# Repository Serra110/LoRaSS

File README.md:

**LoRaSS**

LoRaSS is a custom communication device built around LoRa technology, allowing two (or more) devices to exchange short messages over radio. It features five buttons: four for entering messages using a custom input system and one dedicated button to save or send the composed message, allowing an entire message to be transmitted in a single operation. The device also includes a display to preview outgoing messages and read received ones, as well as an LED and a buzzer to provide visual and audio feedback when messages are received (like a morse code machine).

**Features**

- **LoRa Communication:** Exchange messages wirelessly using LoRa radio technology.
- **Message Input:** Four buttons are used to enter the desired characters.
- **OLED Display:** Preview messages before sending and read incoming messages.
- **Misc:** An LED and a buzzer indicate when a message is received.

**Hardware Design**

The device is powered by a Raspberry Pi Pico (as mentioned in the other repos, it is my favorite board) and uses a LoRa radio module for wireless communication. The PCB integrates the display, buttons, buzzer, LED and antenna circuitry.

**3D Model**

A 3D representation of the project designed in KiCad.

**Schematic**

**Controls**

- **Buttons 1–4:** Enter characters to compose a message.
- **Button 5:** Send it to another device.

**Communication**

**Code**

The firmware runs on the Raspberry Pi Pico and handles message input.

**About the Project**

This project is my first time messing with antennas, and it is also my first experience working with SMD components and designing an antenna section as part of a PCB.

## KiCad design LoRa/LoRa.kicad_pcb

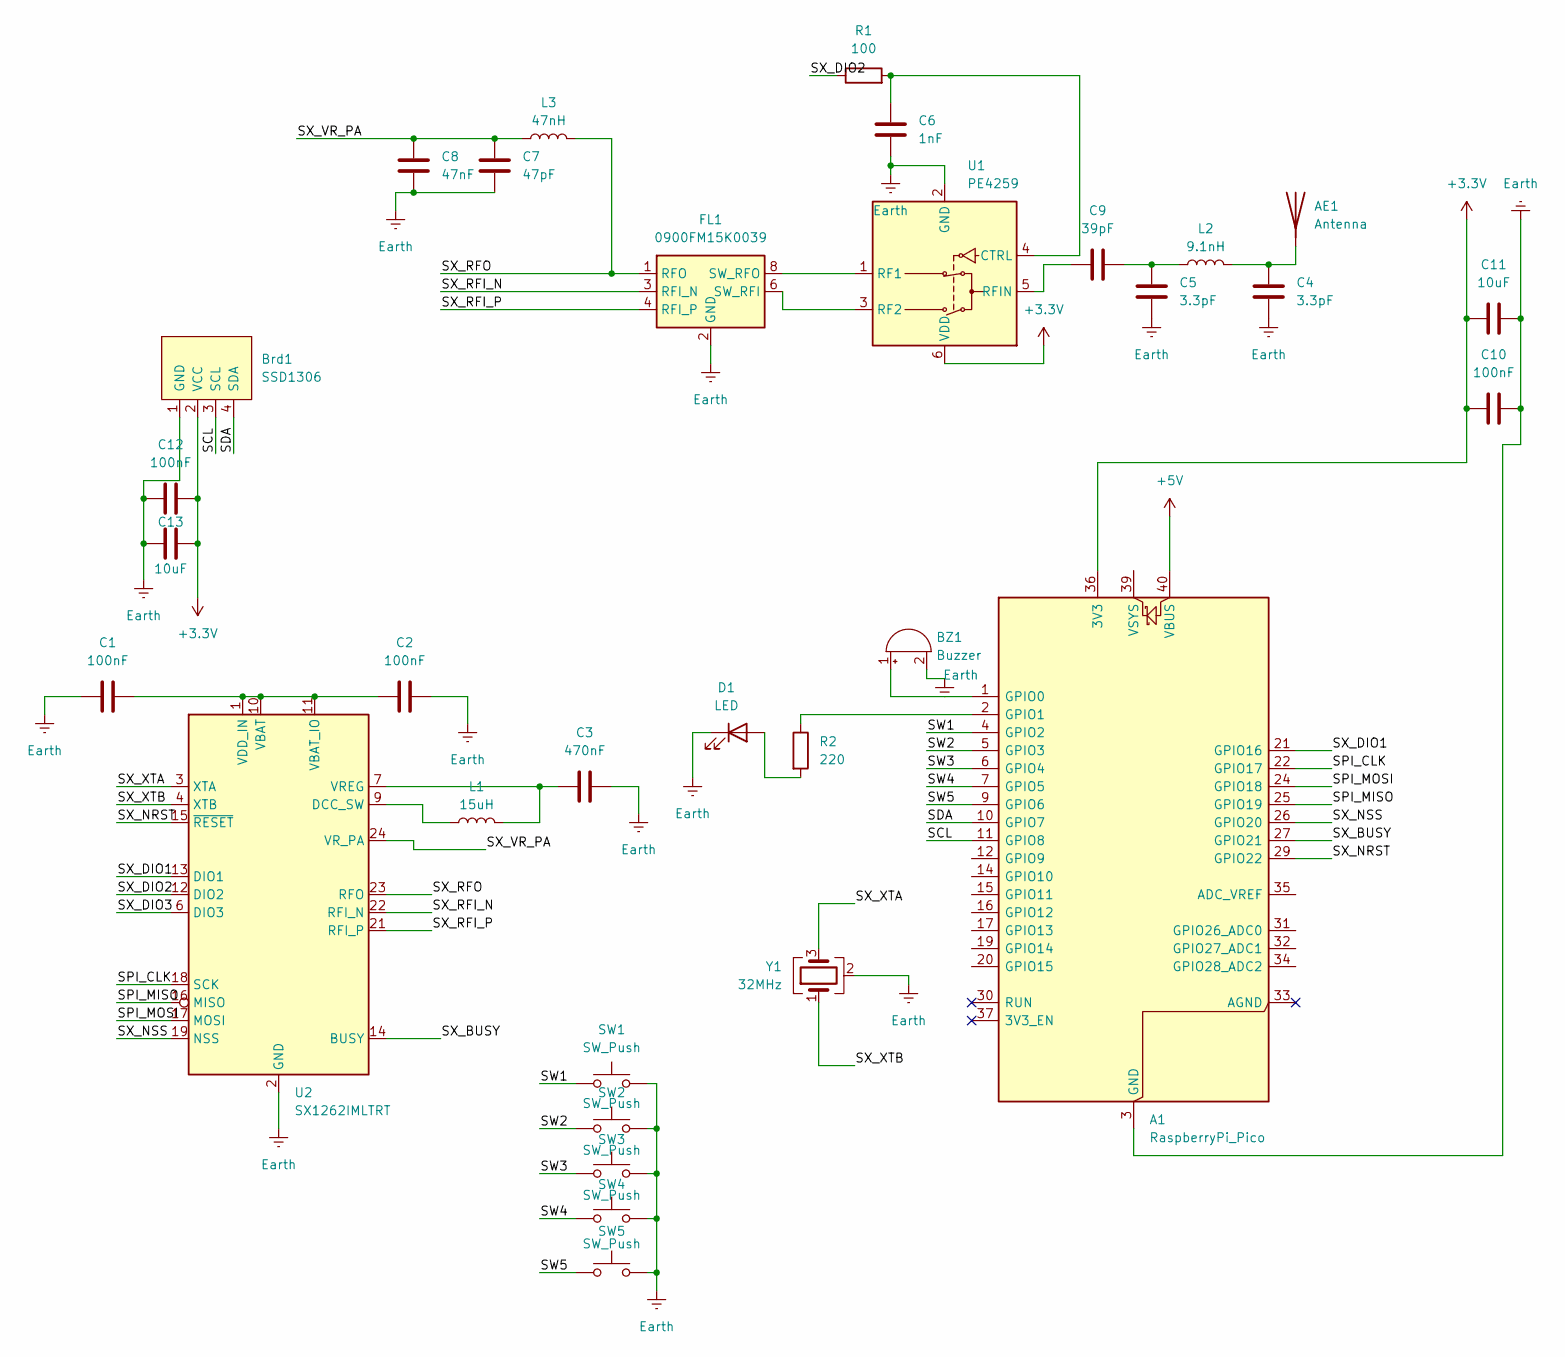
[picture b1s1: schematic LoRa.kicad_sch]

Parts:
A1: RaspberryPi_Pico; RaspberryPi_Pico_Common
AE1: Antenna; PinSocket_1x01_P2.54mm_Vertical
BZ1: Buzzer; Buzzer_12x9.5RM7.6
Brd1: SSD1306; 128x64OLED
C1, C2, C10, C12: 100nF; C_0402_1005Metric
C3: 470nF; C_0402_1005Metric
C4, C5: 3.3pF; C_0402_1005Metric
C6: 1nF; C_0402_1005Metric
C7: 47pF; C_0402_1005Metric
C8: 47nF; C_0402_1005Metric
C9: 39pF; C_0402_1005Metric
C11, C13: 10uF; C_0402_1005Metric
D1: LED; LED_D5.0mm
FL1: 0900FM15K0039; Balun_Johanson_0900FM15K0039
L1: 15uH; L_0402_1005Metric
L2: 9.1nH; L_0402_1005Metric
L3: 47nH; L_0402_1005Metric
R1: 100; R_0402_1005Metric
R2: 220; R_0402_1005Metric
SW1, SW2, SW3, SW4, SW5: SW_Push; SW_PUSH_6mm_H4.3mm
U1: PE4259; SOT-363_SC-70-6
U2: SX1262IMLTRT; QFN-24-1EP_4x4mm_P0.5mm_EP2.6x2.6mm
Y1: 32MHz; Crystal_SMD_3225-4Pin_3.2x2.5mm

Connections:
+3.3V: A1.36 (3V3), Brd1.2 (VCC), C10.1, C11.1, C12.2, C13.2, U1.6 (VDD)
+5V: A1.40 (VBUS)
/SCL: A1.11 (GPIO8), Brd1.3 (SCL)
/SDA: A1.10 (GPIO7), Brd1.4 (SDA)
/SPI_CLK: A1.22 (GPIO17), U2.18 (SCK)
/SPI_MISO: A1.25 (GPIO19), U2.16 (MISO)
/SPI_MOSI: A1.24 (GPIO18), U2.17 (MOSI)
/SW1: A1.4 (GPIO2), SW1.1
/SW2: A1.5 (GPIO3), SW2.1
/SW3: A1.6 (GPIO4), SW3.1
/SW4: A1.7 (GPIO5), SW4.1
/SW5: A1.9 (GPIO6), SW5.1
/SX_BUSY: A1.27 (GPIO21), U2.14 (BUSY)
/SX_DIO1: A1.21 (GPIO16), U2.13 (DIO1)
/SX_DIO2: R1.1, U2.12 (DIO2)
/SX_DIO3: U2.6 (DIO3)
/SX_NRST: A1.29 (GPIO22), U2.15 (~RESET)
/SX_NSS: A1.26 (GPIO20), U2.19 (NSS)
/SX_RFI_N: FL1.3 (RFI_N), U2.22 (RFI_N)
/SX_RFI_P: FL1.4 (RFI_P), U2.21 (RFI_P)
/SX_RFO: FL1.1 (RFO), L3.2, U2.23 (RFO)
/SX_VR_PA: C7.1, C8.1, L3.1, U2.24 (VR_PA)
/SX_XTA: U2.3 (XTA), Y1.3
/SX_XTB: U2.4 (XTB), Y1.1
Earth: A1.3 (GND), A1.8 (GND), A1.13 (GND), A1.18 (GND), A1.23 (GND), A1.28 (GND), A1.38 (GND), BZ1.2 (-), Brd1.1 (GND), C1.1, C2.2, C3.2, C4.2, C5.1, C6.2, C7.2, C8.2, C10.2, C11.2, C12.1, C13.1, D1.1 (K), FL1.2 (GND), FL1.5 (GND), FL1.7 (GND), FL1.9 (GND), FL1.10 (GND), SW1.2, SW2.2, SW3.2, SW4.2, SW5.2, U1.2 (GND), U2.2 (GND), U2.5 (GND), U2.8 (GND), U2.20 (GND), U2.25 (GND), Y1.2 (G), Y1.4 (G)
unnamed: A1.1 (GPIO0), BZ1.1 (+)
unnamed: A1.2 (GPIO1), R2.1
unnamed: AE1.1 (A_1), C4.1, L2.2
unnamed: C5.2, C9.2, L2.1
unnamed: D1.2 (A), R2.2
unnamed: FL1.6 (SW_RFI), U1.3 (RF2)
unnamed: FL1.8 (SW_RFO), U1.1 (RF1)
unnamed: C6.1, R1.2, U1.4 (CTRL)
unnamed: C9.1, U1.5 (RFIN)
unnamed: L1.1, U2.9 (DCC_SW)
unnamed: C1.2, C2.1, U2.1 (VDD_IN), U2.10 (VBAT), U2.11 (VBAT_IO)
unnamed: C3.1, L1.2, U2.7 (VREG)

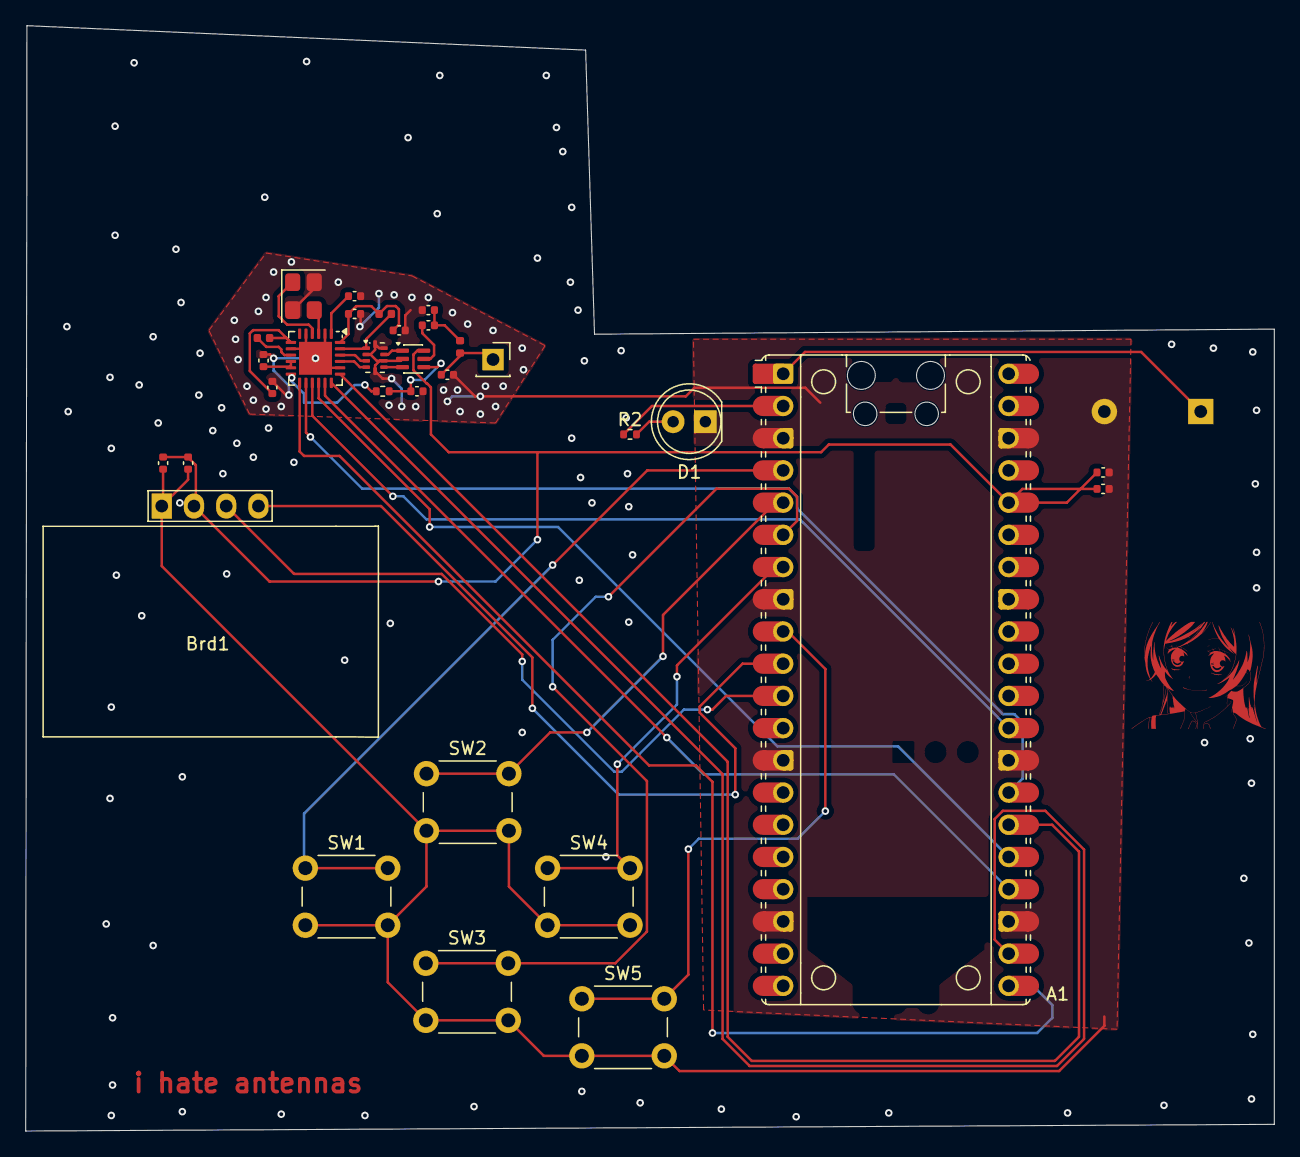
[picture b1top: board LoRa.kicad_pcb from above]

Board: 4 copper layers, 98.5 x 87.2 mm, 32 parts (1 on the bottom side), 35 nets.

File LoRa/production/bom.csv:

Designator,Footprint,Quantity,Value,LCSC Part #
A1,RaspberryPi_Pico_Common,1,RaspberryPi_Pico,
AE1,PinSocket_1x01_P2.54mm_Vertical,1,Antenna,
BRD1,128x64OLED,1,SSD1306,
BZ1,Buzzer_12x9.5RM7.6,1,Buzzer,
"C1, C10, C12, C2",0402,4,100nF,
"C11, C13",0402,2,10uF,
C3,0402,1,470nF,
"C4, C5",0402,2,3.3pF,
C6,0402,1,1nF,
C7,0402,1,47pF,
C8,0402,1,47nF,
C9,0402,1,39pF,
D1,LED_D5.0mm,1,LED,
FL1,Balun_Johanson_0900FM15K0039,1,0900FM15K0039,
L1,0402,1,15uH,
L2,0402,1,9.1nH,
L3,0402,1,47nH,
R1,0402,1,100,
R2,0402,1,220,
"SW1, SW2, SW3, SW4, SW5",SW_PUSH_6mm_H4.3mm,5,SW_Push,
U1,SOT-363_SC-70-6,1,PE4259,
U2,QFN-24-1EP_4x4mm_P0.5mm_EP2.6x2.6mm,1,SX1262IMLTRT,
Y1,Crystal_SMD_3225-4Pin_3.2x2.5mm,1,32MHz,
